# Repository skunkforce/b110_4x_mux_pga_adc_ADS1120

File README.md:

# edgy_board number b110
This design is part of the [edgy board project](https://github.com/skunkforce/edgy_boards). It provides the functionality of the 4xMUX ADC [ADS1120](https://www.digikey.de/de/products/detail/texas-instruments/ADS1120IRVAR/6571556) with PGA.

# getting started
This repository uses submodules. After cloning use the command 

```$ git submodule update --init --recursive```

to pull the submodules before opening the project with kicad. 

# Tests
Tests can be found in [TESTS.md](TESTS.md)

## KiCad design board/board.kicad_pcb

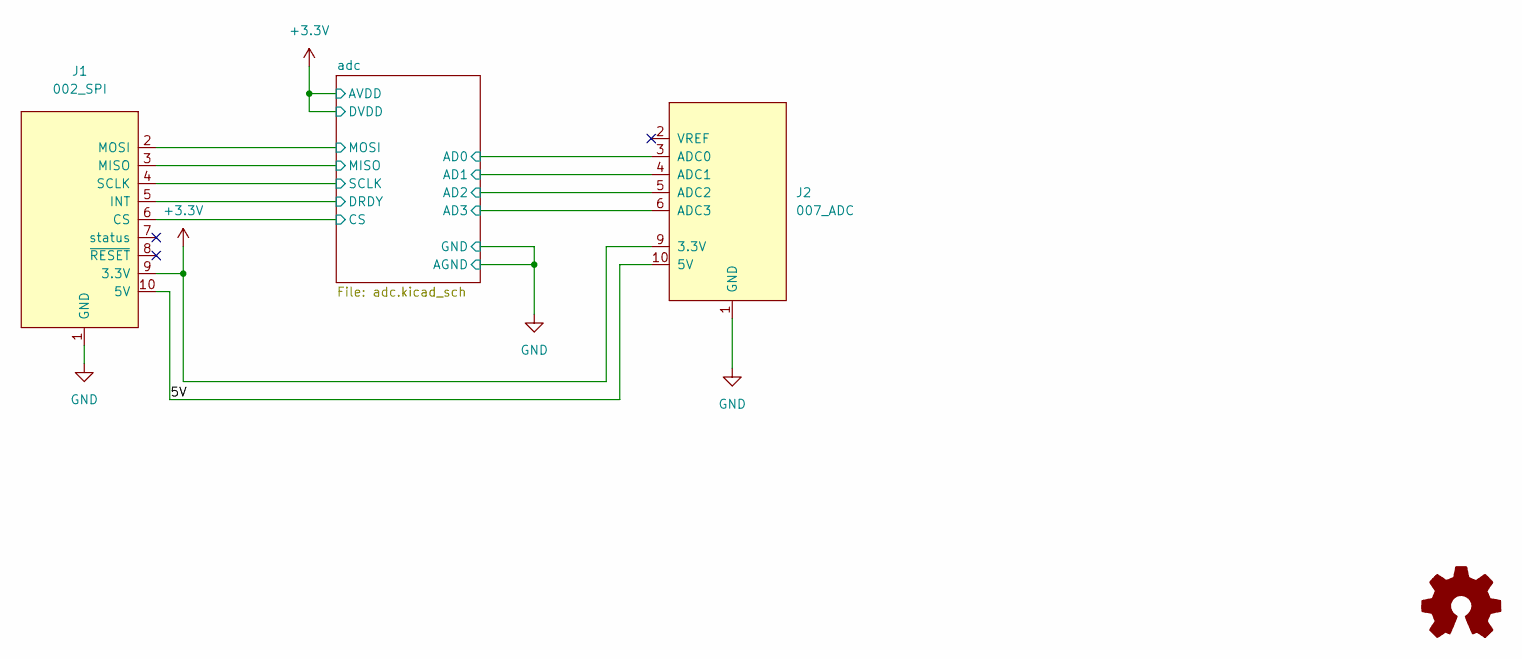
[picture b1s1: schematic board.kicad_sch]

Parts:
J1: 002_SPI; on_edge_2x05_device
J2: 007_ADC; on_edge_2x05_host
LOGO1: Logo_Open_Hardware_Small; OSHW-Symbol_6.7x6mm_SilkScreen

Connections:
+3.3V: J1.9 (3.3V), J2.9 (3.3V); also elsewhere on the board
/5V: J1.10 (5V), J2.10 (5V)
/adc/AD0: J2.3 (ADC0); also elsewhere on the board
/adc/AD1: J2.4 (ADC1); also elsewhere on the board
/adc/AD2: J2.5 (ADC2); also elsewhere on the board
/adc/AD3: J2.6 (ADC3); also elsewhere on the board
/adc/CS: J1.6 (CS); also elsewhere on the board
/adc/DRDY: J1.5 (INT); also elsewhere on the board
/adc/MISO: J1.3 (MISO); also elsewhere on the board
/adc/MOSI: J1.2 (MOSI); also elsewhere on the board
/adc/SCLK: J1.4 (SCLK); also elsewhere on the board
GND: J1.1 (GND), J2.1 (GND); also elsewhere on the board

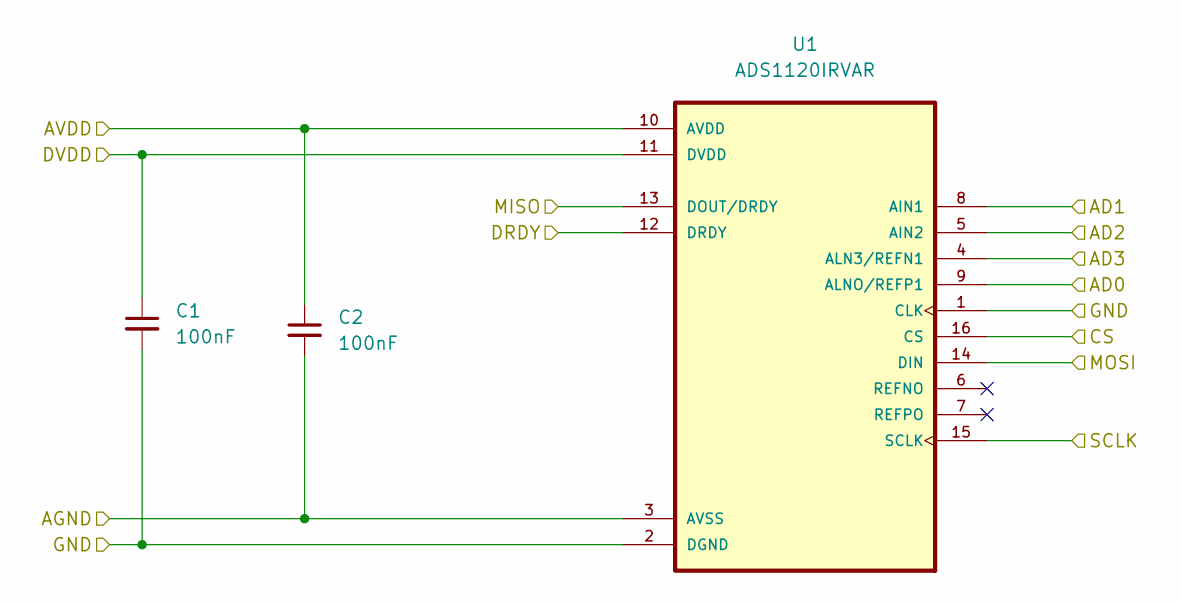
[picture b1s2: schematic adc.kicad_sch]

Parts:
C1, C2: 100nF; C_0603_1608Metric
U1: ADS1120IRVAR; QFN50P350X350X100-17N

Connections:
+3.3V: C1.1, C2.1, U1.10 (AVDD), U1.11 (DVDD); also elsewhere on the board
/adc/AD0: U1.9 (ALNO/REFP1); also elsewhere on the board
/adc/AD1: U1.8 (AIN1); also elsewhere on the board
/adc/AD2: U1.5 (AIN2); also elsewhere on the board
/adc/AD3: U1.4 (ALN3/REFN1); also elsewhere on the board
/adc/CS: U1.16 (CS); also elsewhere on the board
/adc/DRDY: U1.12 (DRDY); also elsewhere on the board
/adc/MISO: U1.13 (DOUT/DRDY); also elsewhere on the board
/adc/MOSI: U1.14 (DIN); also elsewhere on the board
/adc/SCLK: U1.15 (SCLK); also elsewhere on the board
GND: C1.2, C2.2, U1.1 (CLK), U1.2 (DGND), U1.3 (AVSS); also elsewhere on the board

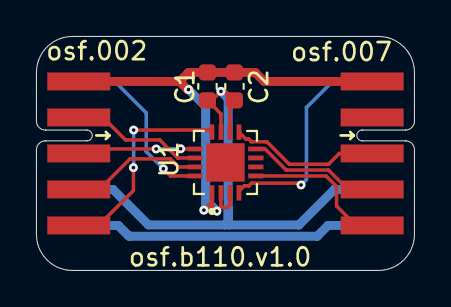
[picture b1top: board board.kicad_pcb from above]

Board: 2 copper layers, 21.0 x 13.0 mm, 6 parts (1 on the bottom side), 12 nets.

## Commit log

2023-03-13 initial
2024-01-09 added jlc production files and some cosmetic changes
